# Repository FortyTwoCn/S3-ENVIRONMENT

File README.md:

# S3-ENVIRONMENT

ESP32-S3 多传感器环境监测项目：可插拔 PCB 底板、ESP32 固件，以及 PHP / PostgreSQL / WebSocket 网站。

底板用 PCB 替代面包板与杜邦线。ESP32-S3、GY-302、BME688、LD2410C 和 MQ 均使用现成模块，通过排母插入，便于维修和更换。

## 当前状态

| 部分 | 版本 / 状态 |
|---|---|
| PCB | R1.1，KiCad 9，110×90 mm，2 层 FR4，1.6 mm，1 oz，4 个 M3 安装孔 |
| PCB 检查 | ERC、DRC、未连接网络、原理图 / PCB 一致性均为 0 问题；自动电气和天线铜区检查通过 |
| PCB 制造文件 | 已提供 Gerber / 钻孔；**MECHANICAL_DIMENSION_PENDING，尚未标记 PRODUCTION VERIFIED** |
| 网络固件 | `carrier-network-1.1.0`（Bosch BSEC2），16MB Flash / 8MB OPI PSRAM，两种 USB 构建版本 |
| 实物验证 | 2026-10-05 经 CH343 / COM4 烧录；Flash / PSRAM、重启自动联网、WSS 上传、PostgreSQL 入库和网页立即采样已通过 |
| 网站 | 已部署至 [s.xuanknow.cn](https://s.xuanknow.cn)，Linux / 宝塔 / Nginx / PHP 8.5 / PostgreSQL，SSL 由宝塔管理 |
| 传感器 | 载板尚未到货；杜邦线接法下 BH1750 / BME688 读取、上传、入库和网页立即采样已通过；MQ 未连接、雷达未供电，完整四传感器测试尚未通过 |

开发板排距 **25.40 mm**、针距 **2.54 mm**，每侧 22Pin。端部偏移、各模块本体尺寸及 USB 插头包络仍需实物确认。打板前按 [硬件说明](hardware/README.md) 核对 [1:1 校验 PDF](hardware/fabrication/ESP32_FOOTPRINT_1_TO_1_CHECK.pdf)，不要把暂定制造文件当作已完成机械验证的版本。

## 仓库目录

```text
S3-ENVIRONMENT/
├── server/                  PHP 网站、API、数据库、WebSocket、邮件 / 清理任务
│   ├── public/              Nginx 网站根目录；CSS / JS / Chart.js
│   ├── src/                 登录、数据校验、实时服务、邮件任务
│   ├── bin/                 初始化、迁移、改密码、地址同步、后台服务
│   ├── database/schema.sql
│   ├── composer.json / composer.lock / vendor/
│   └── .env.example         配置模板；不含真实运行密钥
├── firmware/                Wi-Fi / WSS 主固件，PlatformIO 工程与预编译文件
├── hardware/                完整 KiCad R1.1 工程、封装、3D、BOM、Gerber、审查
│   └── firmware_test/       无网络的传感器串口测试程序
├── deployment/              Nginx / Supervisor / Caddy / Docker / 备份模板
├── docs/                    软件说明、协议、部署记录与实物烧录记录
├── tools/eda/               嘉立创 EDA CLI / MCP 与 Run API Gateway 辅助工具
├── tests/                   隔离数据库的软件集成 / 浏览器测试
├── test_results/            已执行的软件、编译与实物验证结果
├── screenshots/             软件联调与实物截图；模拟数据截图明确标注
├── compose.yaml / compose.production.yaml
├── start_windows.ps1 / stop_windows.ps1
└── SHA256SUMS.txt            仓库内容校验清单
```

## 从哪里开始

- **打开和核对电路板**：[hardware/README.md](hardware/README.md)、[设计摘要](hardware/Design_Summary.md)、[BOM](hardware/fabrication/BOM.csv)、[Excel BOM](hardware/fabrication/BOM_R1_1.xlsx)。用 KiCad 9 打开 `hardware/esp32_sensor_carrier.kicad_pro`。
- **部署网站**：[软件完整说明](docs/software.md)、[实际 Linux / 宝塔部署记录](docs/deployment/s_xuanknow_cn/README.md)。支持 Nginx 直接部署，Docker 是可选方式。
- **烧录 / 配网**：[软件说明](docs/software.md)、[实物烧录记录](docs/device_flash/ESP32S3_COM4/README.md)。常用 USB 转串口版本是 `yd_uart`。
- **用杜邦线测试**：[接线图和步骤](docs/dupont_test/README.md)，包括 MQ 必需保护电路；GPIO 按丝印数字识别。
- **查看通信格式**：[WebSocket 协议](docs/PROTOCOL.md)。
- **维护硬件**：[参数化与检查脚本](hardware/scripts/README.md)。重建布局脚本会产生未布线板，修改尺寸后需要重新布线和导出制造文件。

本仓库保留 Composer 锁文件和 PHP 依赖，以便直接部署；依赖更新通过 Composer 执行。第三方来源及许可证见 [资料说明](docs/SOURCES.md) 和各依赖目录。

## 网站功能

网站使用访问密码登录，可记住登录；支持历史表格、曲线、CSV 导出和设备实时状态。ESP32 正常每 **300 秒**上传一次，断线自动重试，上电自动连接。网页可以请求立即采样，设备完成新的传感器测量后返回记录。

PostgreSQL 默认保留最近 **60 天**，可在网页配置。网页还可设置 SMTP、收件邮箱与烟雾报警策略。SMTP 授权码加密保存；MQ 默认禁用，确认硬件供电、预热和输出极性后再启用。1.0.2 在 MQ 禁用时上传空值，网页显示“未启用”，避免悬空引脚读数被误认为 MQ 测量；旧历史记录保留。

## GPIO 与接口

| 功能 | GPIO | 连接 |
|---|---:|---|
| I2C SDA | 8 | BH1750 / BME688 共用 |
| I2C SCL | 9 | BH1750 / BME688 共用 |
| Radar RX | 17 | LD2410C TX → ESP RX |
| Radar TX | 18 | ESP TX → LD2410C RX |
| Radar OUT | 16 | LD2410C OUT |
| MQ ADC | 4 | AO 经 R1.1 分压、滤波及断电保护 |
| MQ DO | 5 | DO 经 Q1 反相保护，默认 GPIO5 HIGH 表示报警 |
| 普通扩展 | 6、7、10、11 | 3.3V GPIO |
| Servo PWM | 12 | 舵机电源使用独立输入 |

接口针序以 [interface_pinout.csv](hardware/fabrication/interface_pinout.csv) 和方形 Pin1 焊盘为准，尤其注意 R1.1 已修正 GY-302 与 MQ 的顶视安装针序。

BH1750 默认 `0x23`，可改为 `0x5C`；BME688 默认 `0x76`，可改为 `0x77`。MQ AO 分压为 6.8k / 7.5k，GPIO 节点另有 100k 负载和 100nF；固件按这些 R1.1 参数换算。LD2410C 使用 256000 / 8N1 UART。

## Linux / Nginx 部署要点

1. 准备 PHP 8.3+，启用 `pdo_pgsql`、`mbstring`、`sodium`、`openssl`，并创建 PostgreSQL 数据库。
2. 在 `server/` 执行 `composer install --no-dev --prefer-dist --optimize-autoloader`，按 [软件说明](docs/software.md) 初始化 `server/.env`。
3. 设置数据库连接、`APP_URL=https://你的域名`、`WS_PUBLIC_URL=wss://你的域名/ws`、`COOKIE_SECURE=1` 和 `WS_BIND=127.0.0.1`。
4. Nginx 网站根目录指向 **`server/public`**，`/ws` 反代至 `127.0.0.1:8081`；参考 `deployment/nginx.conf.example`。
5. 执行 `php server/bin/migrate.php`，通过 Supervisor 启动唯一的 `server/bin/websocket.php` 与 `server/bin/worker.php`。
6. 进入网页创建设备，把设备专属令牌和 2.4GHz Wi-Fi 信息填写到 ESP32 配网页面。

现有宝塔站点目录直接放置的是 `server/` 的内容，网站运行目录为 `/www/wwwroot/s.xuanknow.cn/public`；克隆本仓库后则是仓库内的 `server/public`。按实际目录调整 Nginx、Supervisor 和 `open_basedir`。

修改网站密码：`php server/bin/password.php`；修改公开地址：`php server/bin/set-public-url.php https://你的域名`。操作后重启后台进程。两项操作均保留设备令牌。

## 编译和烧录固件

在仓库根目录执行：

```sh
python -m pip install platformio
python -m platformio run --project-dir firmware -e yd_uart
python -m platformio run --project-dir firmware -e yd_uart -t upload --upload-port COM4
python -m platformio device monitor --port COM4 --baud 115200
```

Linux 将 `COM4` 改成实际串口，例如 `/dev/ttyUSB0`。原生 USB CDC 版本使用 `yd_native_usb`，与 CH343 调试串口版本分别提供构建产物。

源码和预编译固件不包含实际 Wi-Fi 密码或设备令牌。首次烧录后从串口查看临时配网 AP，打开 `http://192.168.4.1` 配置；已配置设备会自动连接。输入 `CONFIG` 或开机后长按 BOOT 5 秒可重新配置；`STATUS` 可查看连接和传感器诊断；`I2C_SCAN` 扫描地址，`SENSOR_RETRY` 重新初始化两块 I2C 模块，`REBOOT` 重启。

## 配置与验证记录

真实 `.env`、网站密码、设备令牌、SMTP 授权码、SSH 私钥、NVS 配网镜像、数据库与原 Flash 备份均未提交。需要为新的部署生成自己的密钥和设备令牌。实物记录中的 Wi-Fi 名称也已脱敏。

BH1750 / BME688 在 1.0.2 下的历史实测读数、I2C 地址及网页入库验证见 [physical_i2c_1.0.2.json](test_results/physical_i2c_1.0.2.json) 和 [实测页面截图](screenshots/physical_i2c_20261005.png)。

1.0.2 修正接线前的实物烧录、I2C 扫描、MQ 空值入库与立即采样验证见 [physical_bringup_1.0.2.json](test_results/physical_bringup_1.0.2.json)。MQ 显示回归检查：`node tests/mq_display.cjs`；MQ 遥测契约检查：`php tests/telemetry_mq.php`。

1.0.1 的历史物理网络验证见 [physical_website.json](test_results/physical_website.json) 和 [烧录启动检查](test_results/physical_flash.json)。`tests/` 的软件测试使用隔离的 `*_test` 数据库，包含清空测试表的操作；不会默认执行，也不应配置为真实监测数据库。

LD2410C、MQ 及真实烟雾邮件告警仍待实物验证；不能由两块 I2C 传感器通过就认定全部模块通过。硬件的 **MECHANICAL VERIFICATION REQUIRED** 状态保留在全部制造说明中。

固件 1.1.0 增加 Bosch BSEC 的 **eCO₂、bVOC、IAQ、静态 IAQ、相对气体水平、补偿气体信号及未补偿温湿度**，网页支持实时卡片、历史表格、各指标曲线和 CSV。准确度、预热和校准状态不上传；无有效估计时显示空缺。eCO₂ 是等效估计，BME688 不直接测量 CO₂。接口、GPIO 和 PCB 均不变，BSEC 在设备内部按约 3 秒采样，上报仍默认每 5 分钟一次。说明见 [BME688 输出](docs/BME688.md)，实测见 [1.1.0 验证](test_results/physical_bsec_1.1.0.json)。

BSEC 回归检查：`node tests/air_display.cjs`、`php tests/telemetry_air.php`。Bosch 专有算法许可见 [第三方声明](firmware/THIRD_PARTY_NOTICES.md)。

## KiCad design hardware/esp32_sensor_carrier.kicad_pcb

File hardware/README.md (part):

# ESP32-S3 多传感器可插拔载板 R1.1

**MECHANICAL VERIFICATION REQUIRED — MECHANICAL_DIMENSION_PENDING**

本工程已完成原理图、实际双层 PCB 布线、铺铜、制造文件和测试固件。KiCad 9.0.9 实际执行结果：ERC 0 错误/警告，DRC 0 错误/警告，Unconnected 0，原理图/PCB 一致性问题 0。自动网络、电压、模块包络及天线禁布区检查通过。**实物端部偏移、传感器板尺寸/针序及 USB 插头包络尚未物理验证；当前 Gerber 为暂定版，未标记 PRODUCTION VERIFIED。**

这是一块替代面包板和杜邦线的底板。ESP32 开发板、GY-302、BME688、LD2410C、MQ 都是用户提供的成品模块，插入排母，维修时可拔出。底板没有重新设计 ESP32 最小系统，也没有把传感器裸芯片放到底板上。

## 2026-10-02 实物照片复核 - R1.1

新照片保存在 `sources/actual_sensor_modules.jpg`，详细记录在 `checks/sensor_photo_review.md` / `.json`。

**BME688 是连续单排 1×6，针距 2.54 mm，首末针中心距 12.70 mm；原工程已采用这个排列。** 用户确认照片背面左→右为 **CS / SDO / SDA / SCL / GND / VCC**。本工程让感测面向上，模块本体位于排针上方，因此底板顶视左→右为 **VCC / GND / SCL / SDA / SDO / CS**，原 BME 接口无需修改。

GY-302 与 MQ 照片也显示背面。R1 的两个接口沿用了背面顺序，感测面朝上且本体保持当前区域时，顺序必须镜像。**R1.1 已修正 J2=ADDR / SDA / SCL / GND / VCC，J5=VCC / GND / DO / AO**，相应焊盘、原理图、铜线、丝印、CSV 和制造输出同时更新。GPIO 功能不变。不要使用 R1 的旧接线表和制造文件。

**装配方式仍按平放设计：公针从模块背面向下，插入底板竖直排母。** 照片中 MQ 的 90° 弯针不能直接按此方式平放插入，需要换为直针；BME/GY 也必须检查针脚是否满足向下插入要求。保留弯针而让模块站立，会改变模块的碰撞包络、光窗、进气口和雷达朝向，需要另做机械布局，不能套用当前平放校验图。雷达的五个孔在照片中没有装排针，需要在背面焊装 1×5 直针，保持天线面朝上。

雷达的正面天线图形和 TX / RX / OUT / GND / VCC 排列与厂家 LD2410C 手册一致。GY 的部分针名、MQ 的 VCC 丝印在照片中被排针/电位器遮住，镜像处理结合了本项目已有完整针名，**逐脚实物核对仍为 PENDING**。这张照片没有毫米标尺，也不能完成模块尺寸、高度、排针焊接方向的物理验证。

## 文件与打开方式

用 **KiCad 9** 打开 `esp32_sensor_carrier.kicad_pro`，再打开原理图和 PCB。实际生成并验证的格式为 KiCad 9；如使用 KiCad 8，请先在 KiCad 9 中转换/另存并重新检查，不能保证 KiCad 8 直接读取全部 KiCad 9 字段。符号和封装库随工程提供，`sym-lib-table`、`fp-lib-table` 使用 `${KIPRJMOD}` 相对路径，13 个标准 STEP 模型和 5 个暂定模块包络模型也随工程提供。

| 路径 | 内容 |
|---|---|
| `esp32_sensor_carrier.kicad_sch` | A2、七个功能分区的可编辑原理图 |
| `esp32_sensor_carrier.kicad_pcb` | 已完成布线/铺铜的 110×90 mm 双层载板 |
| `mechanical_parameters.json` | 开发板排距、针距、外形和待验证偏移参数 |
| `footprints/custom.pretty/ESP32-S3_N16R8_44PIN_CARRIER.kicad_mod` | 专用 44Pin 整板载板封装 |
| `fabrication/BOM.csv` | 底板器件、排母、跳帽，以及单独标出的用户模块 |
| `fabrication/gpio_map.csv`、`interface_pinout.csv`、`esp32_pinout.csv` | GPIO、各接口针序、44 个开发板脚位 |
| `fabrication/netlist.csv`、`netlist.xml` | 人可读网络表与 KiCad 实际导出的 XML 网络表 |
| `fabrication/ESP32_FOOTPRINT_1_TO_1_CHECK.pdf` | A4 两页，100% 打印的开发板及全板机械校验图 |
| `fabrication/schematic.pdf`、`assembly.pdf` | 原理图和焊接元件定位图 |
| `gerber/PROVISIONAL_MECHANICAL_DIMENSION_PENDING/` | 七个 Gerber 层、独立 PTH/NPTH 钻孔及 SVG 钻孔图 |
| `checks/` | 原始 ERC/DRC、自动审查、Gerber 检查及两种固件编译记录 |
| `images/` | 原理图、PCB 正背面、3D、Gerber/Cu 图及 PDF 渲染预览 |
| `firmware_test/` | PlatformIO Arduino 源代码、两种 USB 预编译固件 |
| `sources/footprint_sources.md` | 公共库/官方尺寸对比及所有电气资料来源 |

CSV 使用 UTF-8 BOM，便于 Windows Excel 正确显示。先看 `Design_Summary.md`，再按照本文件进行装配。

## PCB 与布局

- 最大外形 **110×90 mm**，FR4、1.6 mm、双层、每面 1 oz 铜；常规工艺，无特殊阻抗/盲埋孔。
- 四角 4×3.2 mm M3 非金属化孔，中心 `(4,4), (106,4), (4,86), (106,86)` mm。
- 下方中央 31 mm 宽 USB 开口，从 y=64.5 延伸到 y=90，给双 Type-C 插头让位。
- ESP32 位于中央，天线端朝板顶，USB 端朝中央开口。其他模块不会覆盖 BOOT/RST 所在整板区域。
- GY-302 左上方靠边；BME688 右上方靠边；LD2410C 左下方靠边；MQ 右下方靠边。
- BME688 与 MQ 暂定中心距约 37.5 mm，板体之间留约 10.6 mm。BME 区域减少铺铜，下面有 **20×1 mm、圆头热隔离槽**。槽不是割断整块板，连接排针仍有足够的 FR4 支承。
- 默认信号 0.30 mm。SENSOR_5V 主干、MQ 分支、外部电源/舵机主干为 1.00 mm。Q2 SOT-23 源极处仅有总长约 1.76 mm 的 0.601 mm 局部引出线，其余 EXT_5V 为 1.00 mm。它在 1 A 下的铜损耗很小，最终 DRC 也通过。
- 信号过孔 0.80/0.40 mm，电源过孔 1.20/0.60 mm；规则不小于用户要求的常规安全尺寸。最小铜间距 0.20 mm，电源类 0.25 mm，铜到板边 0.30 mm。
- 上下 GND 铺铜，通过接地过孔及大量接地通孔连接。两个天线区均禁止两面铜、走线、焊盘和过孔。导出的 Gerber 已由独立解析器检查，天线区铜像素为零。

## ESP32 开发板与专用封装

用户照片显示 **CH343P、双 Type-C、BOOT/RST、GPIO48 RGB、S3-N16R8、双排各 22Pin**，外观与 YD-ESP32-S3 系列一致。模组上的 N16R8 表示 16 MB Flash、8 MB PSRAM，不能用无线模组 SMD 封装代替整个开发板载板封装。

采用 `custom:ESP32-S3_N16R8_44PIN_CARRIER`，底板实际焊 **2×1x22、2.54 mm 直插排母**，不焊死开发板。建议所有传感器排母和 ESP 排母选择 **本体高度至少 8.5 mm** 的同类直插产品，确保插入后模块底面不压到低矮的底板元件。排母焊脚对应 1.0 mm 钻孔、1.8 mm 焊盘，第一脚为方形焊盘。

| 参数 | 当前值 | 依据/状态 |
|---|---:|---|
| 每侧针数 | 22 | 照片和 2100 mil 跨度一致 |
| 针距 | 2.54 mm | 照片 21 个间隔跨 53.34 mm |
| HEADER_ROW_SPACING | **25.40 mm** | 照片明确标注 1000 mil / 25.40 mm |
| 矩形板宽 | 27.94 mm | 照片 1100 mil / 27.94 mm |
| 矩形 PCB 长 | 57.15 mm | 照片 2250 mil / 57.15 mm |
| 包含突出天线总长 | 63.389002 mm | 照片 2495.63 mil，精确单位换算 |
| 天线端矩形板边到第一脚 | 暂定 **1.905 mm** | 未确认；不是照片比例估算的实测值 |
| 最后一脚到 USB 端边缘 | 暂定 **1.905 mm** | 未确认；暂按剩余长度等分 |

必须核对的五项：两排中心距、PCB 总宽、PCB 总长、第一脚到矩形顶边偏移、最后一脚到 USB 端边缘偏移。还应核对天线突出部分和 USB 插头外壳。现有资料能确定排距/针距，却不能证明端部偏移相等。

**公共库三重核对结果为 PENDING，不能写 MECHANICALLY VERIFIED。** EasyEDA 的两项已知公共资源已取得并逐项查看，第一项排距 23.114 mm 且右排只找到 21 个孔，第二项及 Espressif 官方资料排距 22.86 mm；都与照片 25.40 mm 不符。本项目因此根据照片的显式尺寸重建专用封装，保留毫米精度。完整名称、资源 ID、官方图链接及拒用原因见 `sources/footprint_sources.md`。

编号约定：元件面正视、天线上方、USB 下方，**左排从上至下 1…22，右排从上至下 23…44**；不是绕封装一圈的 DIP 编号。两排从天线端到 USB 端的丝印如下：

```text
左：3V3 3V3 RST 4 5 6 7 15 16 17 18 8 3 46 9 10 11 12 13 14 5V GND
右：GND TX43 RX44 1 2 42 41 40 39 38 37 36 35 0 45 48 47 21 20 19 GND GND
```

GPIO19/20 保留给 USB；GPIO35/36/37 不接底板电路；GPIO0/3/45/46 不作为扩展；GPIO48 保留给板载 RGB；GPIO43/44 留给 CH343P 调试串口。未使用的开发板引脚在原理图中明确 No Connect。GPIO 分配没有改变用户指定的七个主功能。

## GPIO 与接口

| 功能 | ESP32 GPIO | 底板路径 |
|---|---:|---|
| I2C SDA | 8 | J2.2、J3.4、J7.3 |
| I2C SCL | 9 | J2.3、J3.3、J7.4 |
| Radar RX，接 LD TX | 17 | J4.1 → R9 → U1 通道 1 → GPIO17 |
| Radar TX，接 LD RX | 18 | GPIO18 → U1 通道 2 → R10 → J4.2 |
| Radar OUT | 16 | J4.3 → R11 → U1 通道 3 → GPIO16 |
| MQ ADC | 4 | J5.4 → 分压/滤波 → U1 通道 4 → GPIO4 |
| MQ DO | 5 | J5.3 → Q1 NMOS 反相保护 → GPIO5 |
| 普通扩展 | 6、7、10、11 | J8/J9/J10/J11 的第 3 脚 |
| Servo PWM | 12 | R18 1k → J12.3 |

所有排针序号以方形焊盘/Pin1 端为起点，按 2.54 mm 间距向后数。不要仅凭模块“名字”确定方向，实物丝印必须逐脚匹配。

| 接口 | Pin1 → 最后一脚 | 电压/用途 |
|---|---|---|
| J2，GY-302/BH1750 排母 | ADDR / SDA / SCL / GND / VCC | VCC=3V3；感光区域朝上，PCB 边缘留 LIGHT WINDOW |
| J3，BME688 排母 | VCC / GND / SCL / SDA / SDO / CS | VCC=3V3；CS 经 10k 上拉到 3V3 |
| J4，LD2410C 排母 | TX / RX / OUT / GND / VCC | VCC=SENSOR_5V，3.3V UART/OUT |
| J5，MQ 排母 | VCC / GND / DO / AO | VCC=SENSOR_5V，AO/DO 均有保护 |
| J6，外部传感器输入端子 | EXT_5V_RAW / GND | 稳压 5V ONLY，经 Q2 反接保护 |
| JP3，电源选择 | USB / SENSOR / EXT | 一枚跳帽；1–2 USB，2–3 EXT |
| J7，EXT_I2C | 3V3 / GND / SDA / SCL | 可接 3.3V OLED 等 I2C 模块 |
| J8 / J9 / J10 / J11 | GND / 3V3 / GPIO6、7、10、11 | 3.3V GPIO；仅预留接口，没有蜂鸣器/继电器驱动 |
| J12，Servo | GND / 5V_SERVO / SIGNAL | SIGNAL=GPIO12；电源只来自独立 J13 |
| J13，Servo 电源端子 | SERVO_5V_RAW / GND | 稳压 5V ONLY，经 Q3 反接保护 |

GPIO 扩展脚不能直接驱动继电器线圈或大电流蜂鸣器；后续模块需自带驱动。I2C OLED 若自带上拉，仍需检查总线上拉等效值。

Servo SIGNAL 是 **3.3V 输出预留**，没有5V信号转换器；使用接受3.3V信号、且不会把SIGNAL上拉到5V或反向供电的舵机/驱动模块。普通GPIO扩展也仅允许3.3V逻辑。

## 电源树与选择跳帽

```text
ESP32 USB → 开发板内部电源 → ESP32_5V ─→ JP3 pin1
                          └→ +3V3 → GY-302、BME688、逻辑/扩展、3V3 LED

J6 外部 5V → Q2 PMOS 反接保护 → EXT_5V ─→ JP3 pin3
                                      JP3 pin2 = SENSOR_5V
                                          ├→ MQ heater/module
                                          ├→ LD2410C
                                          └→ 滤波、5V LED、U1 SEL 控制

J13 独立舵机 5V → Q3 PMOS → 5V_SERVO → J12 pin2
所有电源负极与底板 GND 相连。
```

**推荐首次完整测试使用 B 模式：ESP32 自己接 USB，传感器接 J6 外部 5V，JP3 跳帽放 2–3。** 外部输入建议能力至少 5V 1A，推荐稳压 5V 2A，额定范围按 5V±5% 设计。输出电流能力大不会“强行灌入”器件，实际由负载决定。载板传感器及舵机独立支路分别按 **1A 连续** 使用，非大功率配电板。

A 模式：关掉所有电源后，将唯一跳帽移到 JP3 1–2，只用 ESP32 USB 给 SENSOR_5V 供电。**照片没有开发板 USB 路径的电流额定资料，因此 A 模式能否带满 MQ+LD+Wi-Fi 负载取决于实物 USB 线、电源及开发板 5V 路径容量，未作满载实测。** 观察 5V 压降/复位，容量不足用 B 模式。

B 模式：跳帽 2–3，J6 接独立 5V。EXT_5V 只给传感器，不会自动给 ESP32 或 USB 供电。ESP32 仍需自己的 USB；3V3 由它的稳压器提供。JP3 铜网络彼此独立，严禁焊成三个脚同时导通、严禁放两枚跳帽。换跳帽/插拔模块先断电。

下面按全部工作时的**设计预留**计算，不是未知型号模块的实测电流：

| 负载 | 5V侧设计预留 | 供电来源 |
|---|---:|---|
| ESP32 Wi-Fi/BT/Flash/PSRAM、开发板电路 | 0.60A | ESP USB |
| GY/BME/逻辑与少量扩展 | 0.05A | ESP板3V3，计入ESP USB负载 |
| MQ模块/加热器 | 0.50A | SENSOR_5V |
| LD2410C及5V指示/余量 | 0.30A | SENSOR_5V |
| 合计，不含舵机 | **1.45A** | A模式全部走USB；B模式USB约0.65A、外部约0.80A |

因此传感器支路按1A连续、外部电源推荐5V2A；MQ实际电流必须在首板确认。按35um铜、1.00mm线宽、100mm路径估算铜电阻约0.049Ω，1A时压降约49mV、铜损耗约49mW；实际路径长度各异，还需加连接器和PMOS压降，最终以满载TP1测量为准。

Q2/Q3 为 AO3401A，Gate=GND、Source=保护后输出、Drain=输入；正确接法的体二极管先向输出充电，再由低电阻 MOS 导通，避免串联肖特基的大压降。它们是反接保护，不能替代稳压器。

SENSOR_5V 入口有 C3 100uF 电解+C4 10uF+C5 100nF；雷达附近 C6/C7；MQ 附近 C8/C9；3V3 总线 C10/C11。U1 本地 C2 100nF；舵机支路 C12/C13。D1=3V3 绿灯，D2=SENSOR_5V 黄灯，均为 2.2k 限流。D1 被移到下边缘，减轻对 BH1750 光照测量的影响；如需要黑暗测量，可不装 LED。

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
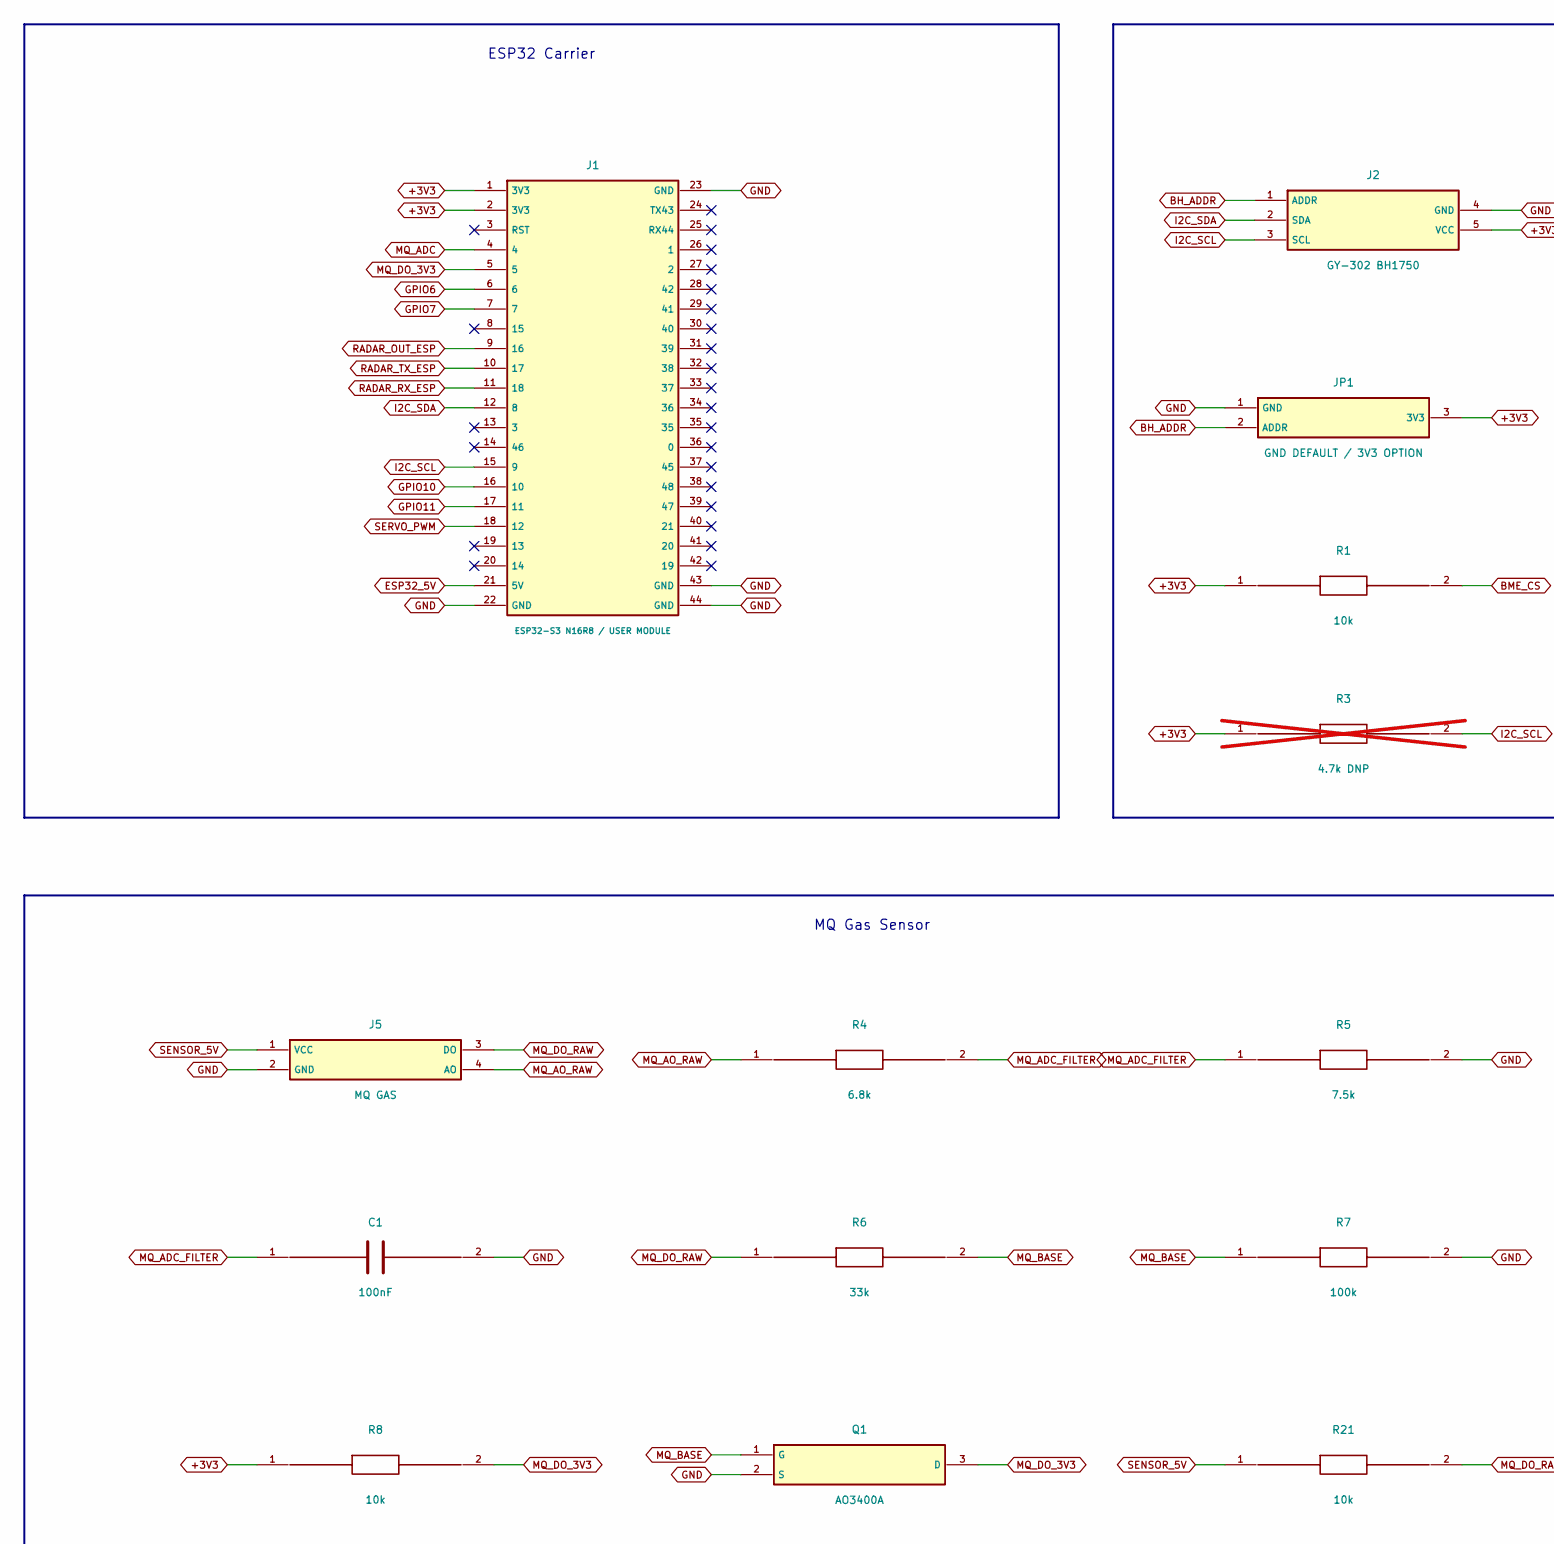
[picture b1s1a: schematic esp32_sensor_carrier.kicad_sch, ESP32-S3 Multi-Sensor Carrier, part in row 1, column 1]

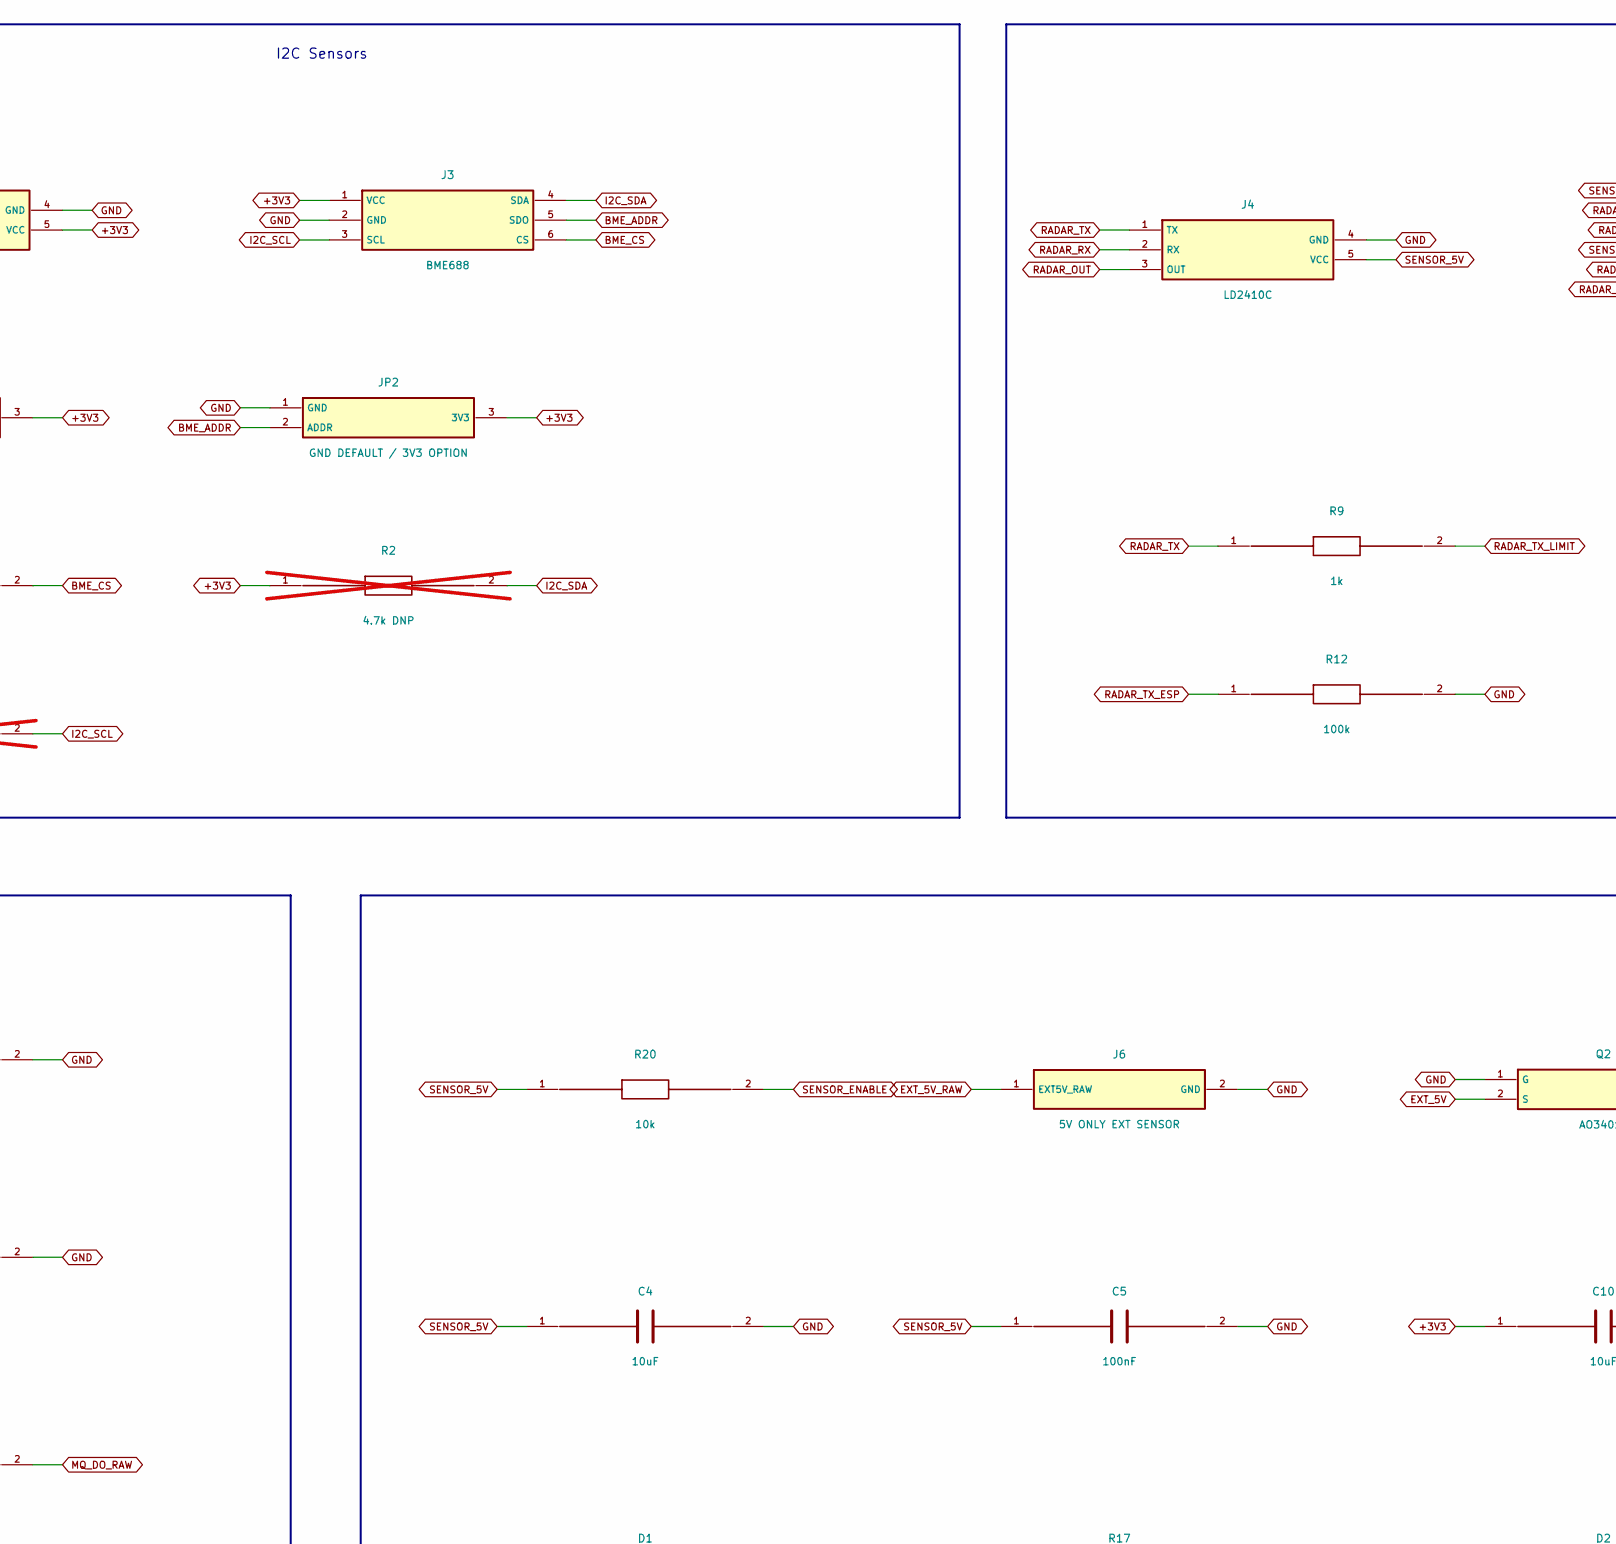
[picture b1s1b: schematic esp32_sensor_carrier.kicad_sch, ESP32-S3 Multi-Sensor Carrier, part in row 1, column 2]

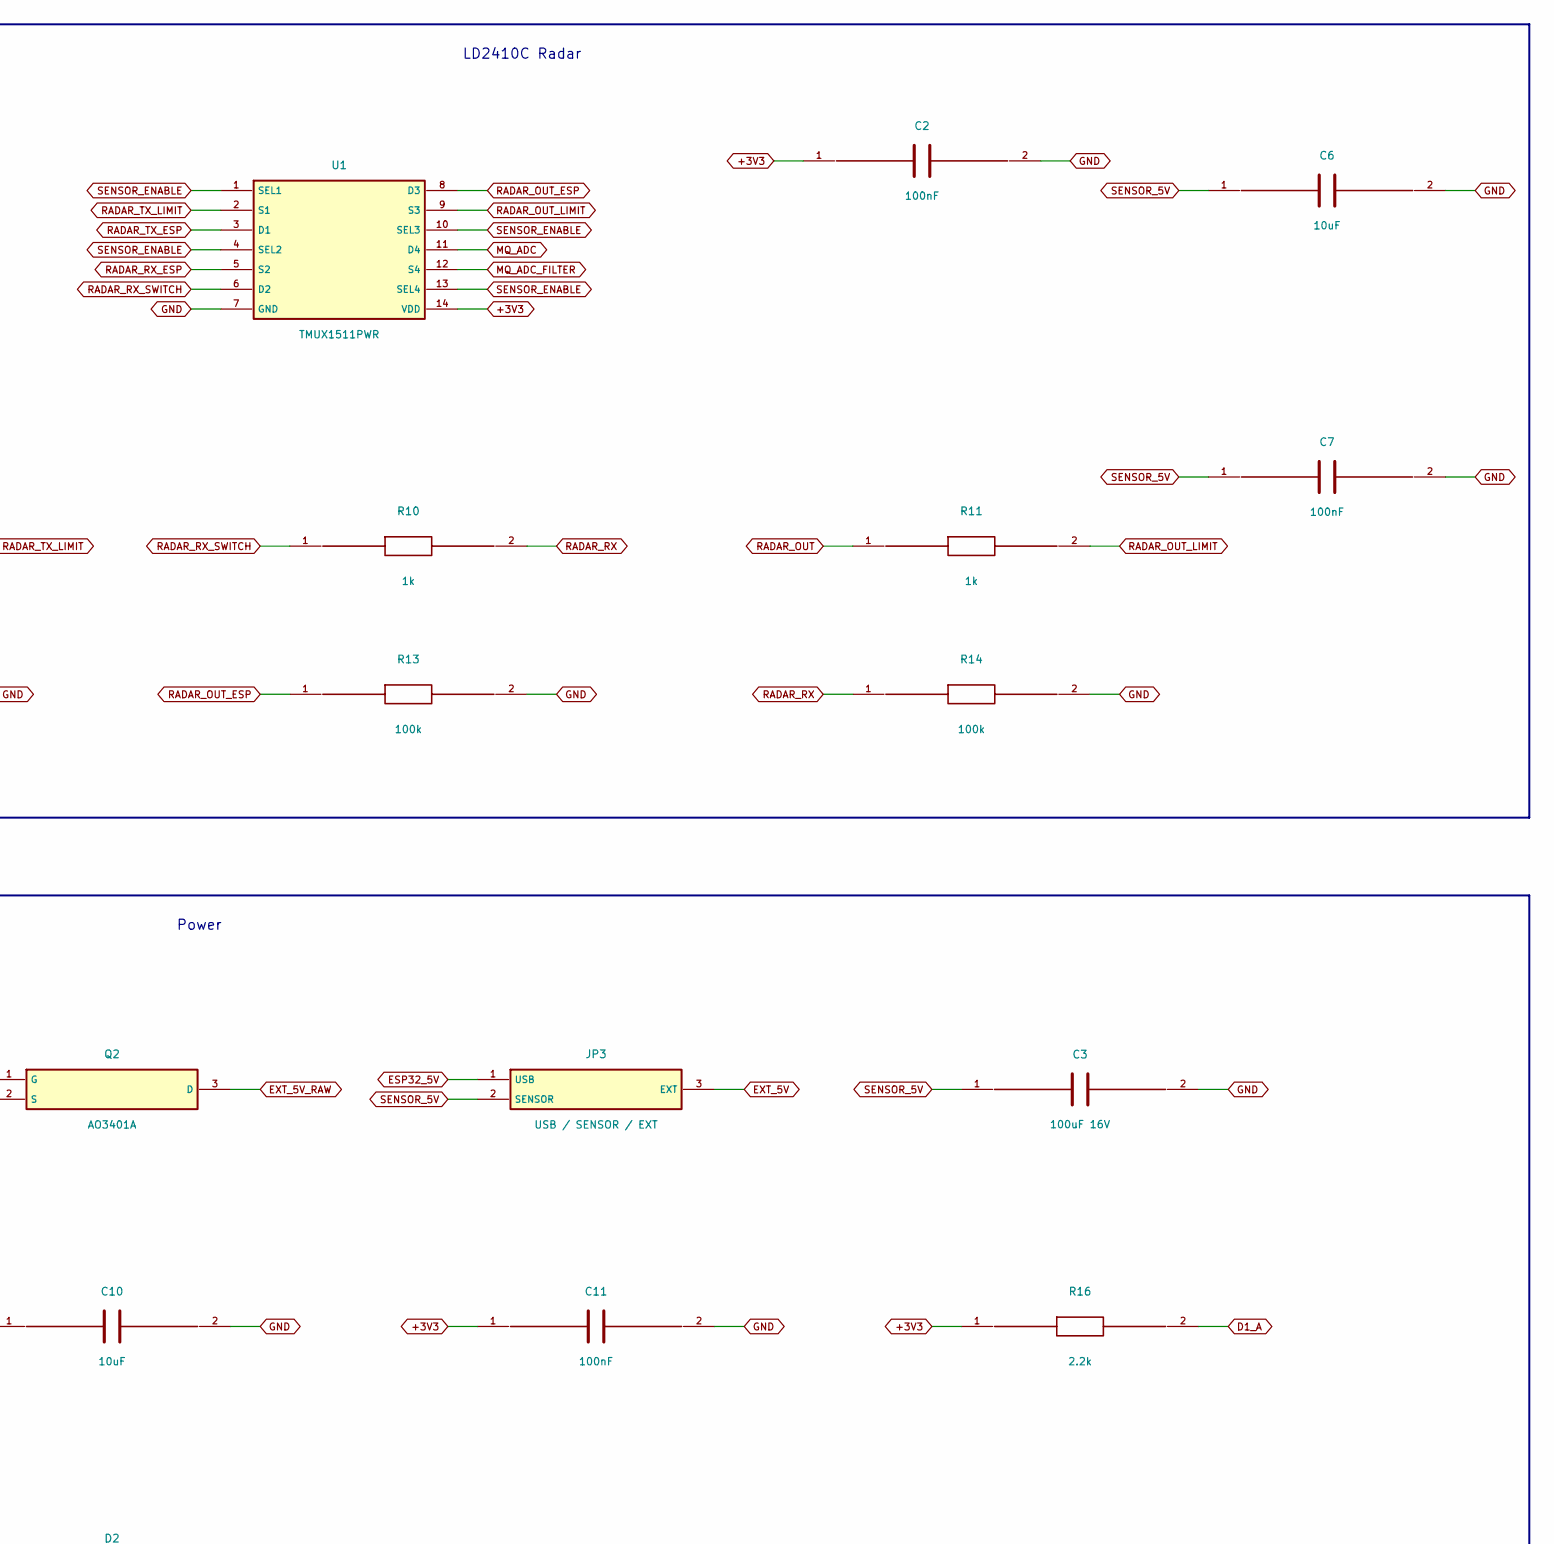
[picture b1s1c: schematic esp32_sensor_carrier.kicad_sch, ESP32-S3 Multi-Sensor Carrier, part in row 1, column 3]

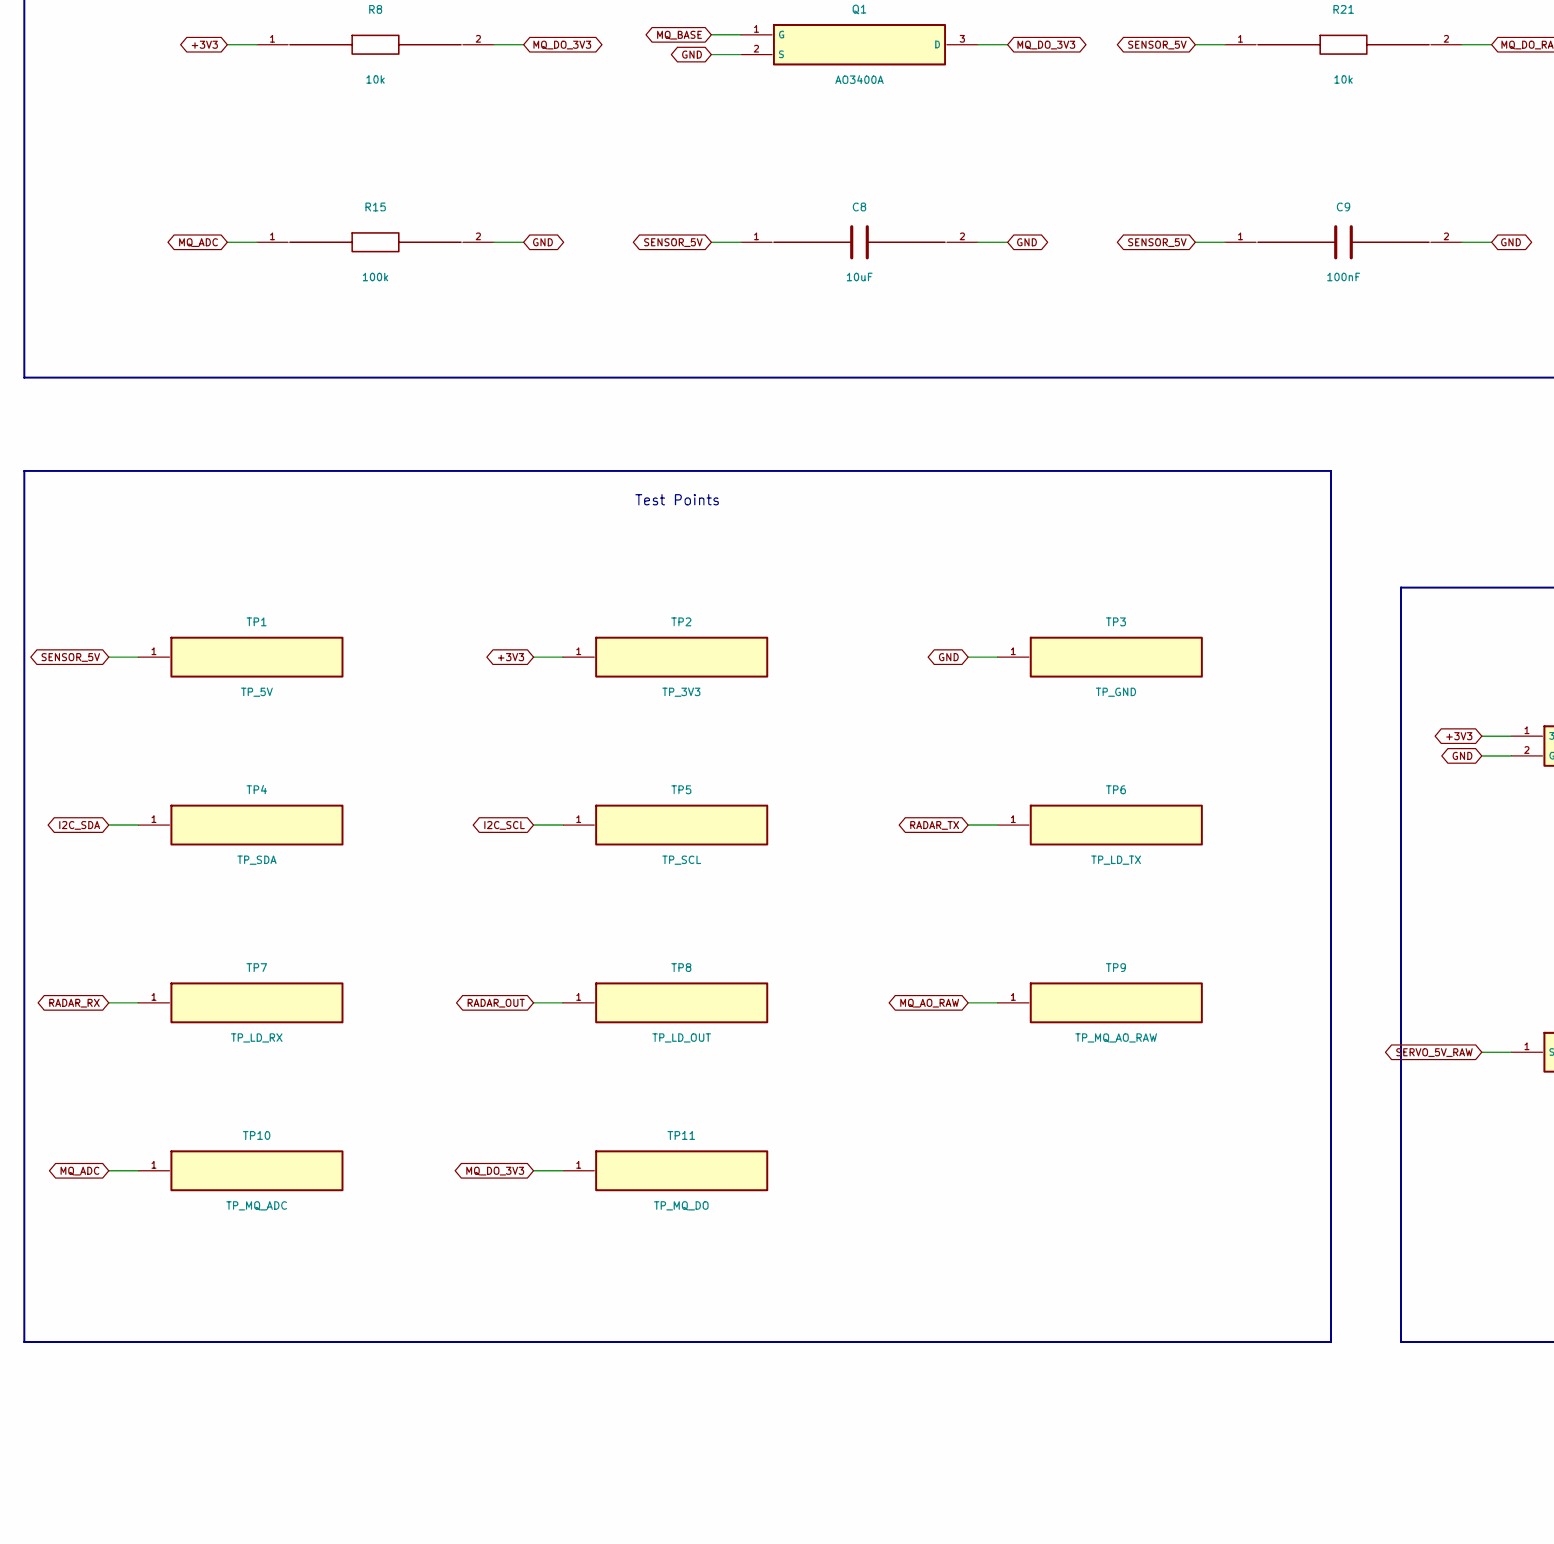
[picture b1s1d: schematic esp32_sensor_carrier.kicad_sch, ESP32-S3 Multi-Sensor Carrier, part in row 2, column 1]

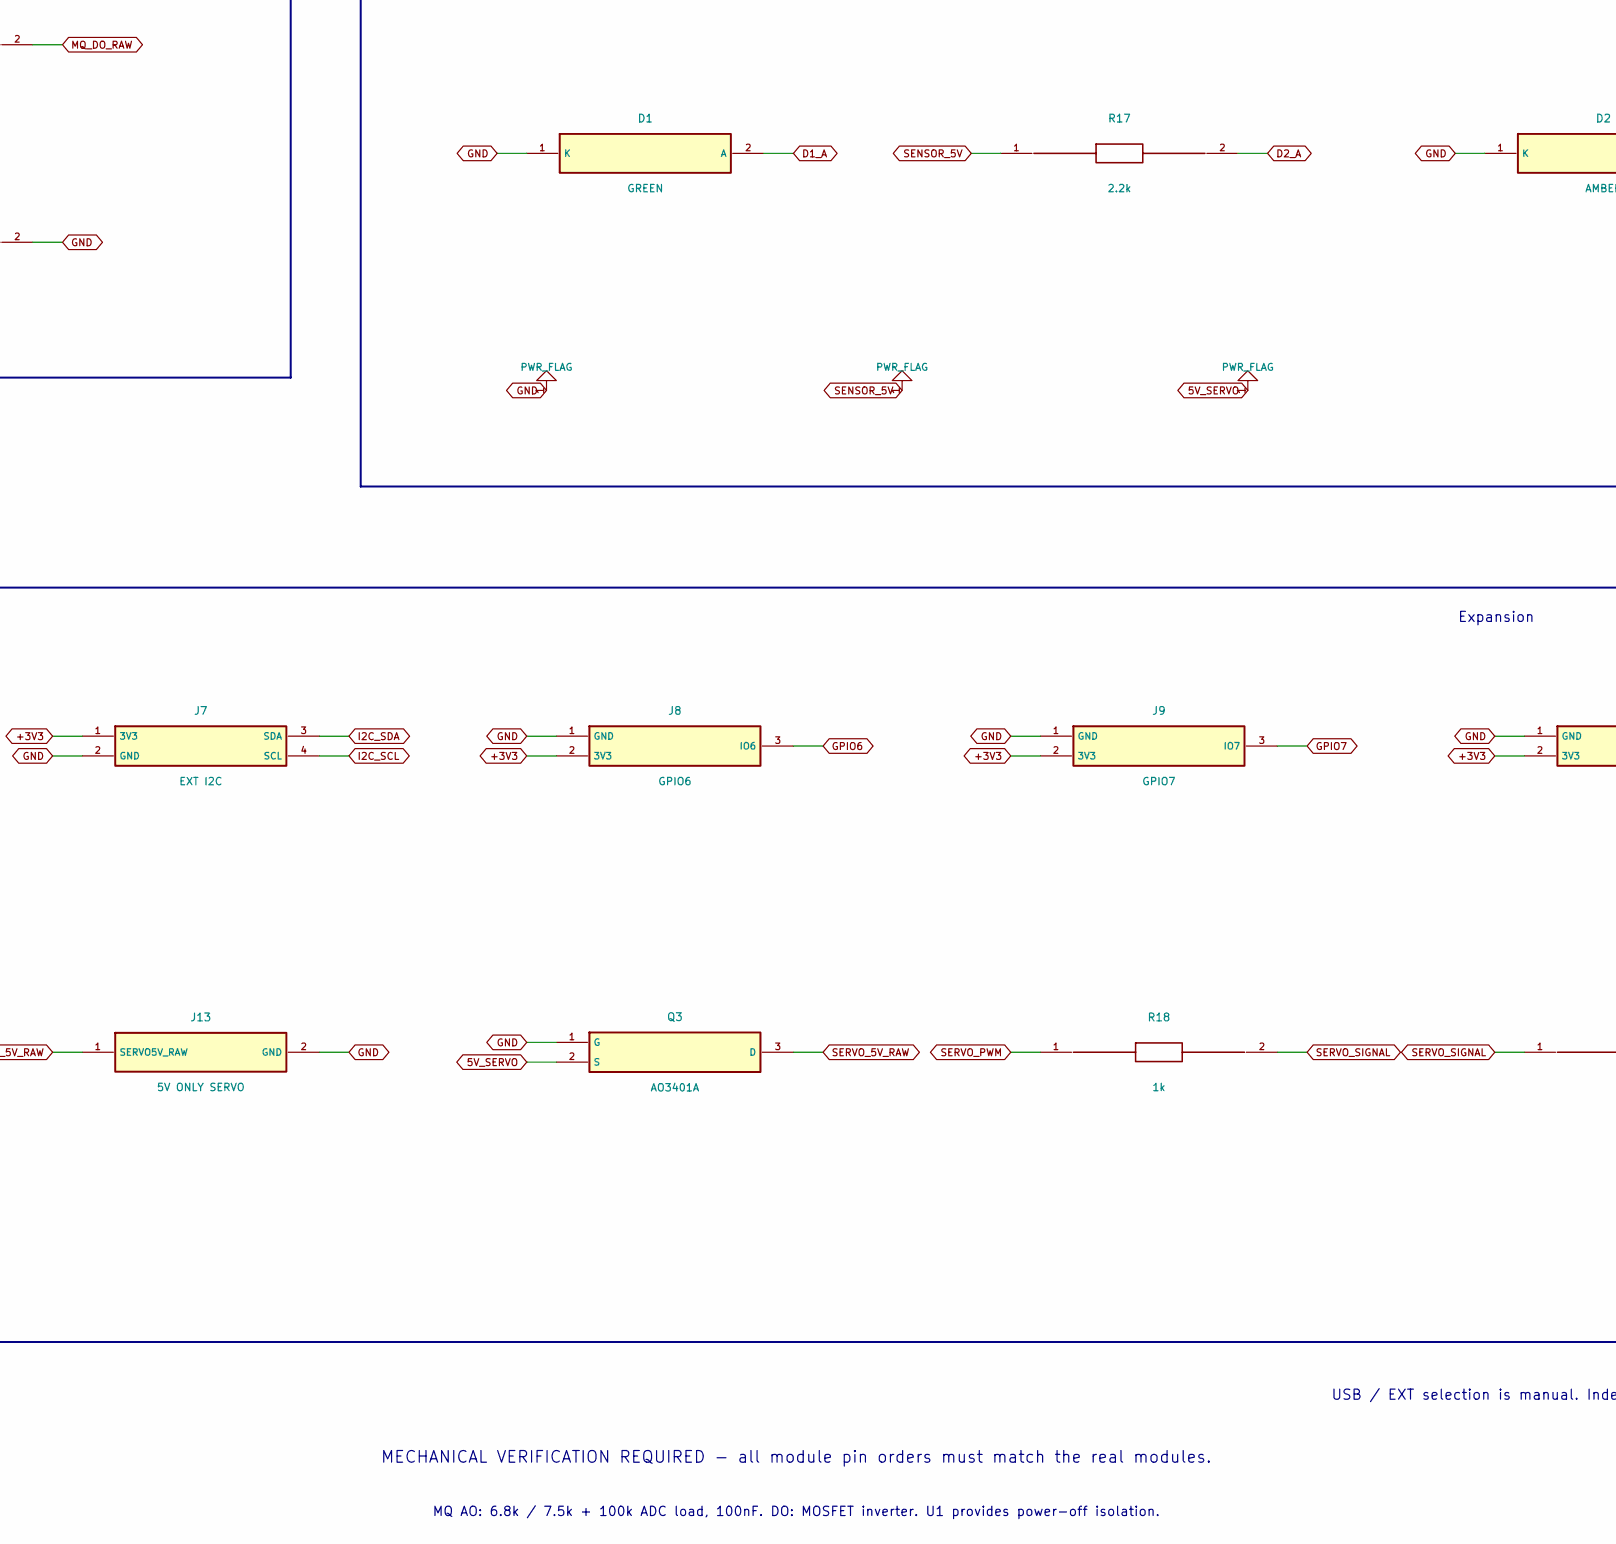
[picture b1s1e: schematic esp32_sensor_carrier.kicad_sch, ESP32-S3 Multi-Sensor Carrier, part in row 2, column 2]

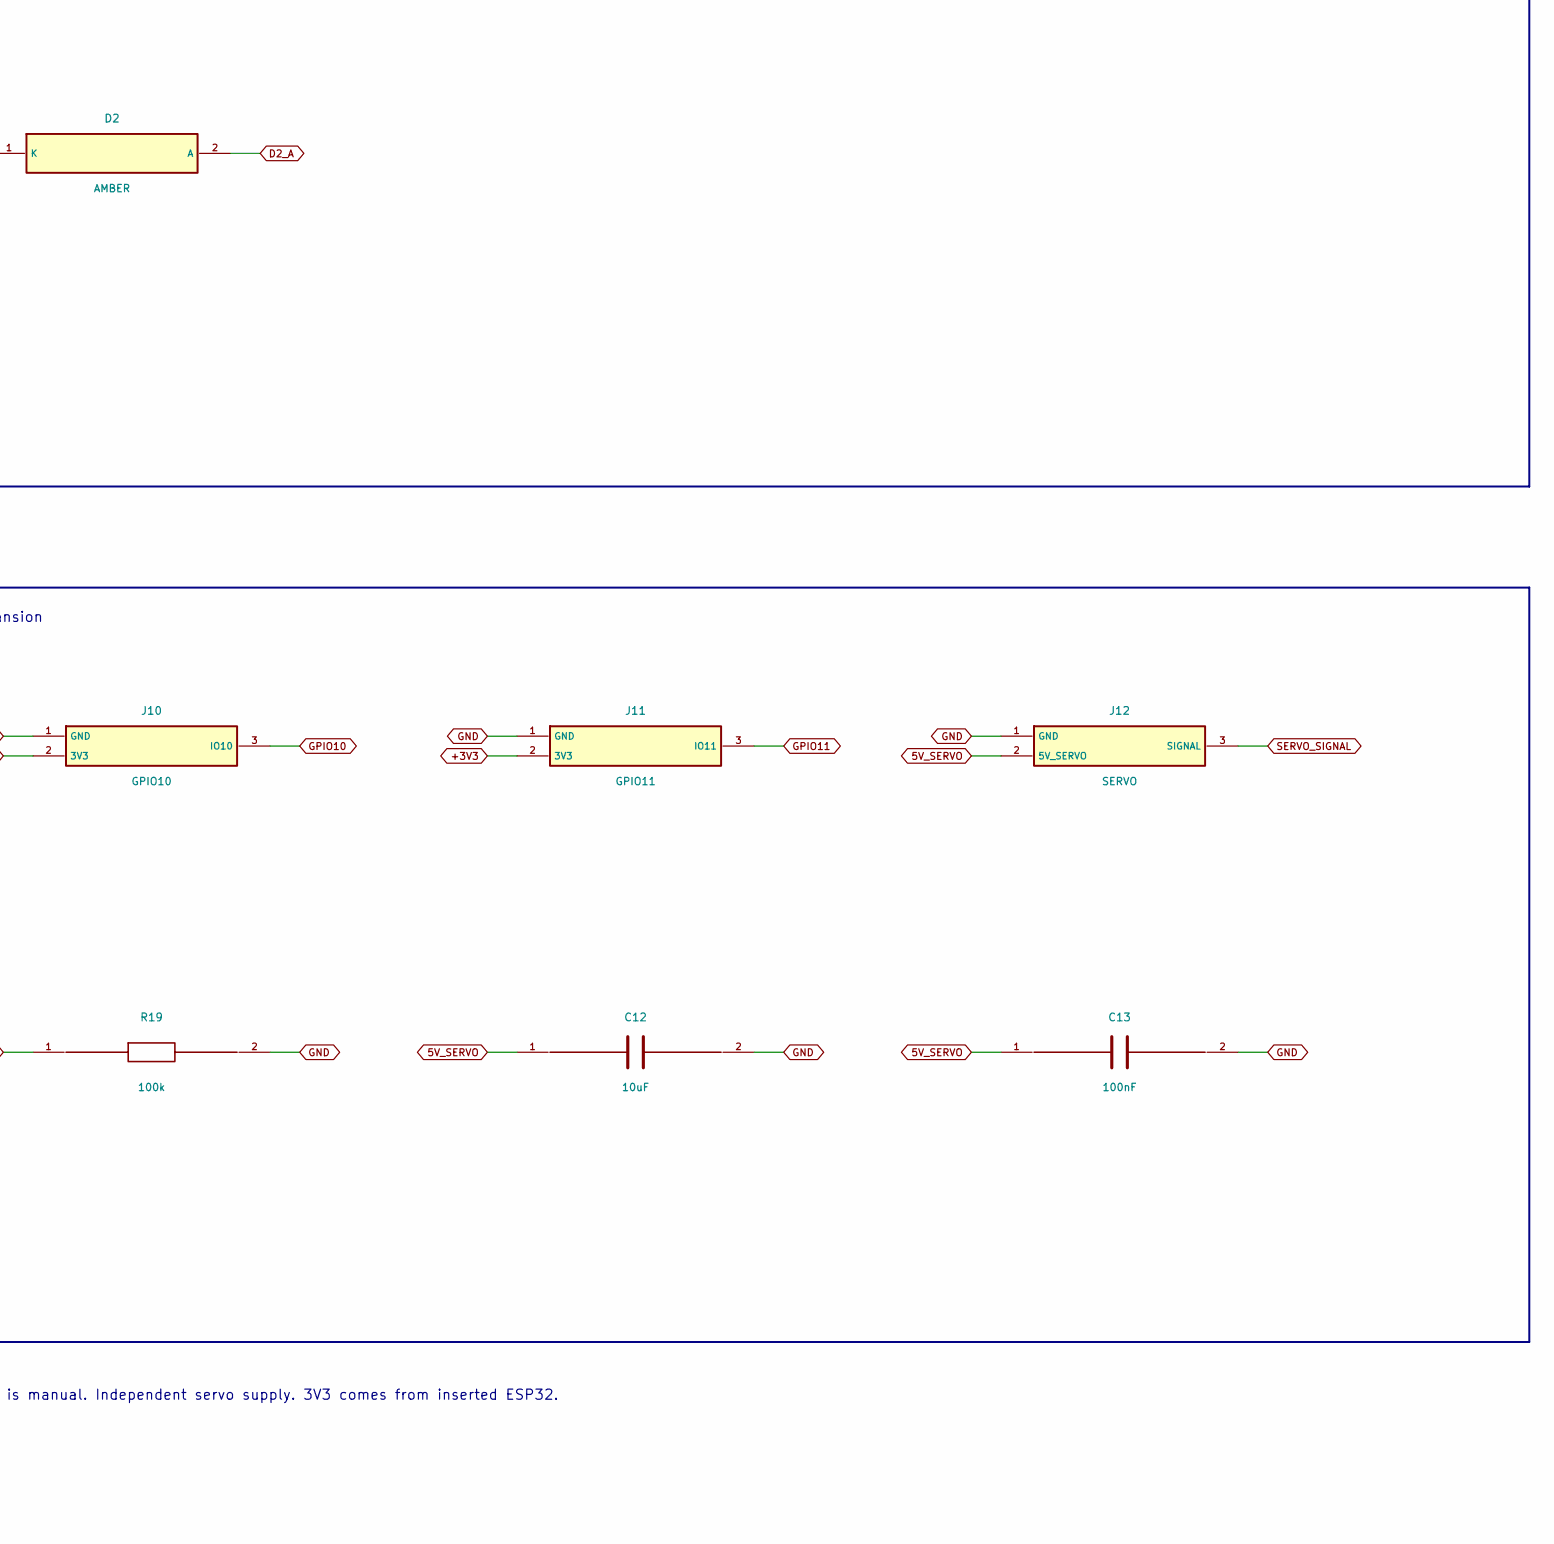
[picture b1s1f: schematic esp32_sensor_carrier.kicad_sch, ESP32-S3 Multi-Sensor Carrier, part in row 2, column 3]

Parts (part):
C1, C2, C5, C7, C9, C11, C13: 100nF; C_1206_3216Metric
C3: 100uF 16V; CP_Radial_D6.3mm_P2.50mm
C4, C6, C8, C10, C12: 10uF; C_1206_3216Metric
D1: GREEN; LED_1206_3216Metric
D2: AMBER; LED_1206_3216Metric
J1: ESP32-S3 N16R8 / USER MODULE; ESP32-S3_N16R8_44PIN_CARRIER
J2: GY-302 BH1750; GY-302_BH1750_SOCKET
J3: BME688; BME688_SOCKET
J4: LD2410C; LD2410C_SOCKET
J5: MQ GAS; MQ_GAS_SOCKET
J6: 5V ONLY EXT SENSOR; TerminalBlock_Phoenix_MKDS-1,5-2-5.08_1x02_P5.08mm_Horizont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
J7: EXT I2C; EXT_I2C_1x04
J8: GPIO6; GPIO_1x03
J9: GPIO7; GPIO_1x03
J10: GPIO10; GPIO_1x03
J11: GPIO11; GPIO_1x03
J12: SERVO; SERVO_1x03
J13: 5V ONLY SERVO; TerminalBlock_Phoenix_MKDS-1,5-2-5.08_1x02_P5.08mm_Horizont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
JP1, JP2: GND DEFAULT / 3V3 OPTION; SolderJumper-3_P1.3mm_Bridged12_RoundedPad1.0x1.5mm
JP3: USB / SENSOR / EXT; POWER_SELECT_1x03
Q1: AO3400A; SOT-23
Q2, Q3: AO3401A; SOT-23
R1, R8, R20, R21: 10k; R_1206_3216Metric
R2, R3: 4.7k DNP; R_1206_3216Metric; not fitted
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
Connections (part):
5V_SERVO: C12.1 (+), C13.1 (+), J12.2 (5V_SERVO), Q3.2 (S)
+3V3: C2.1 (+), C10.1 (+), C11.1 (+), J1.1 (3V3), J1.2 (3V3), J2.5 (VCC), J3.1 (VCC), J7.1 (3V3), J8.2 (3V3), J9.2 (3V3), J10.2 (3V3), J11.2 (3V3), JP1.3 (3V3), JP2.3 (3V3), R1.1, R2.1, R3.1, R8.1, R16.1, TP2.1, U1.14 (VDD)
BH_ADDR: J2.1 (ADDR), JP1.2 (ADDR)
BME_ADDR: J3.5 (SDO), JP2.2 (ADDR)
BME_CS: J3.6 (CS), R1.2
D1_A: D1.2 (A), R16.2
D2_A: D2.2 (A), R17.2
ESP32_5V: J1.21 (5V), JP3.1 (USB)
EXT_5V: JP3.3 (EXT), Q2.2 (S)
EXT_5V_RAW: J6.1 (EXT5V_RAW), Q2.3 (D)
GND: C1.2 (GND), C2.2 (GND), C3.2 (-), C4.2 (GND), C5.2 (GND), C6.2 (GND), C7.2 (GND), C8.2 (GND), C9.2 (GND), C10.2 (GND), C11.2 (GND), C12.2 (GND), C13.2 (GND), D1.1 (K), D2.1 (K), J1.22 (GND), J1.23 (GND), J1.43 (GND), J1.44 (GND), J2.4 (GND), J3.2 (GND), J4.4 (GND), J5.2 (GND), J6.2 (GND), J7.2 (GND), J8.1 (GND), J9.1 (GND), J10.1 (GND), J11.1 (GND), J12.1 (GND), J13.2 (GND), JP1.1 (GND), JP2.1 (GND), Q1.2 (S), Q2.1 (G), Q3.1 (G), R5.2, R7.2, R12.2, R13.2, R14.2, R15.2, R19.2, TP3.1, U1.7 (GND)
GPIO6: J1.6, J8.3 (IO6)
GPIO7: J1.7, J9.3 (IO7)
GPIO10: J1.16 (10), J10.3 (IO10)
GPIO11: J1.17 (11), J11.3 (IO11)
I2C_SCL: J1.15 (9), J2.3 (SCL), J3.3 (SCL), J7.4 (SCL), R3.2, TP5.1
I2C_SDA: J1.12 (8), J2.2 (SDA), J3.4 (SDA), J7.3 (SDA), R2.2, TP4.1
MQ_ADC: J1.4, R15.1, TP10.1, U1.11 (D4)
MQ_ADC_FILTER: C1.1 (+), R4.2, R5.1, U1.12 (S4)
MQ_AO_RAW: J5.4 (AO), R4.1, TP9.1
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
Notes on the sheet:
ESP32 Carrier
I2C Sensors
LD2410C Radar
MQ Gas Sensor
Power
Expansion
Test Points
USB / EXT selection is manual. Independent servo supply. 3V3 comes from inserted ESP32.
MECHANICAL VERIFICATION REQUIRED - all module pin orders must match the real modules.
MQ AO: 6.8k / 7.5k + 100k ADC load, 100nF. DO: MOSFET inverter. U1 provides power-off isolation.
